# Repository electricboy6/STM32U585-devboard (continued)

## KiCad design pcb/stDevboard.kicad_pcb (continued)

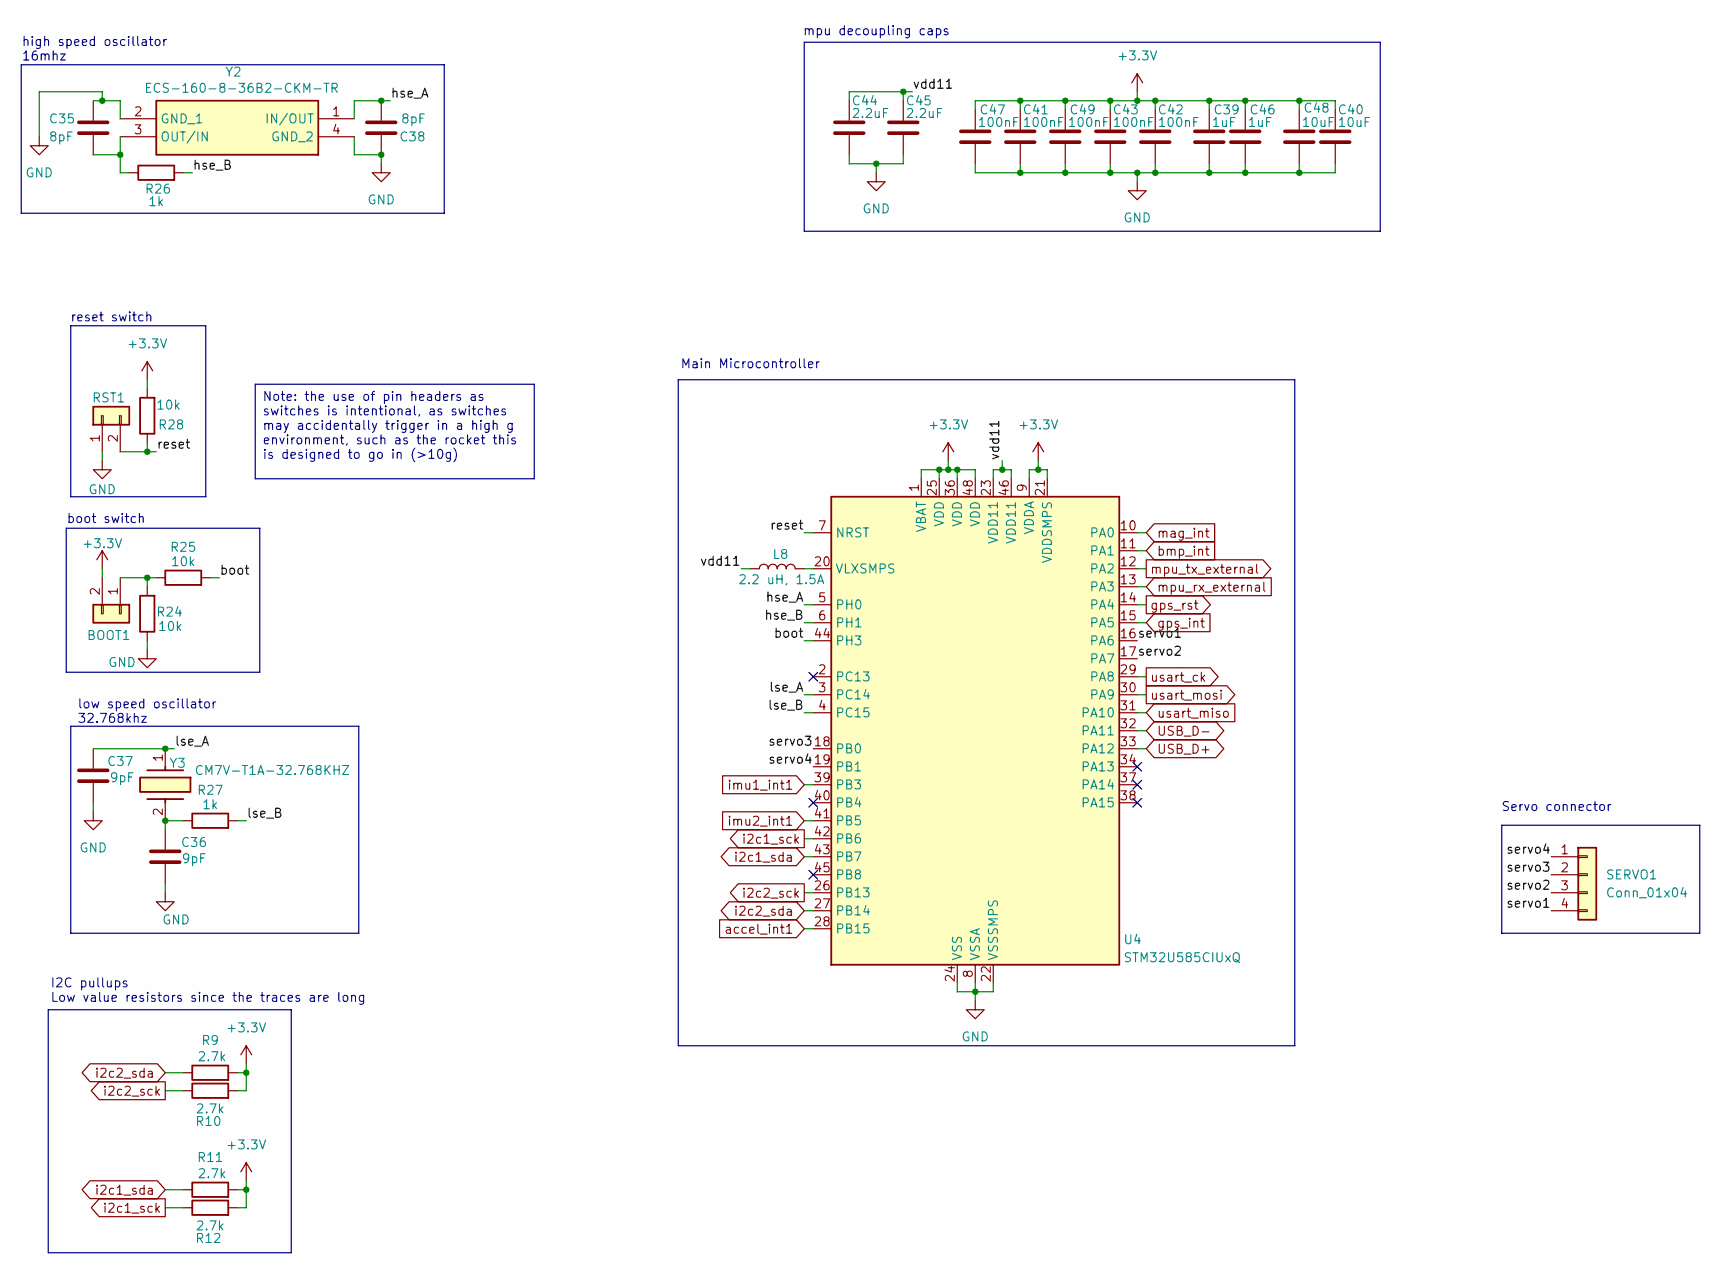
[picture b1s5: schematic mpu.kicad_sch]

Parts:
BOOT1: Conn_01x02; PinHeader_1x02_P2.54mm_Vertical
C35, C38: 8pF; C_0402_1005Metric
C36, C37: 9pF; C_0402_1005Metric
C39, C46: 1uF; C_0603_1608Metric
C40, C48: 10uF; C_0603_1608Metric
C41, C42, C43, C47, C49: 100nF; C_0402_1005Metric
C44, C45: 2.2uF; C_0603_1608Metric
L8: 2.2 uH, 1.5A; INDC2520X120N
R9, R10, R11, R12: 2.7k; R_0402_1005Metric
R24, R25, R28: 10k; R_0402_1005Metric
R26, R27: 1k; R_0402_1005Metric
RST1: Conn_01x02; PinHeader_1x02_P2.54mm_Vertical
SERVO1: Conn_01x04; TBC05041GG
U4: STM32U585CIUxQ; QFN-48-1EP_7x7mm_P0.5mm_EP5.6x5.6mm
Y2: ECS-160-8-36B2-CKM-TR; ECS160836B2CKMTR; Mouser Part Number 520-160-8-36B2-CKMTR
Y3: CM7V-T1A-32.768KHZ; CM7V32768TBQA020; Mouser Part Number 428-201565-MG01

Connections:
/main micro/boot: R25.2, U4.44 (PH3)
/main micro/hse_A: C38.1, U4.5 (PH0), Y2.1 (IN/OUT)
/main micro/hse_B: R26.2, U4.6 (PH1)
/main micro/lse_A: C37.1, U4.3 (PC14), Y3.1
/main micro/lse_B: R27.2, U4.4 (PC15)
/main micro/reset: R28.1, RST1.2, U4.7 (NRST)
/main micro/servo1: SERVO1.4, U4.16 (PA6)
/main micro/servo2: SERVO1.3, U4.17 (PA7)
/main micro/servo3: SERVO1.2, U4.18 (PB0)
/main micro/servo4: SERVO1.1, U4.19 (PB1)
/main micro/vdd11: C44.1, C45.1, L8.1, U4.23 (VDD11), U4.46 (VDD11)
GND: C35.2, C36.2, C37.2, C38.2, C39.2, C40.2, C41.2, C42.2, C43.2, C44.2, C45.2, C46.2, C47.2, C48.2, C49.2, R24.1, RST1.1, U4.8 (VSSA), U4.22 (VSSSMPS), U4.24 (VSS), U4.35 (VSS), U4.47 (VSS), U4.49 (VSS), Y2.2 (GND_1), Y2.4 (GND_2); also elsewhere on the board
unnamed: BOOT1.1, R24.2, R25.1
unnamed: C36.1, R27.1, Y3.2
unnamed: L8.2, U4.20 (VLXSMPS)
unnamed: C35.1, R26.1, Y2.3 (OUT/IN)
USB_D+: U4.33 (PA12); also elsewhere on the board
USB_D-: U4.32 (PA11); also elsewhere on the board
accel_int1: U4.28 (PB15); also elsewhere on the board
bmp_int: U4.11 (PA1); also elsewhere on the board
gps_int: U4.15 (PA5); also elsewhere on the board
gps_rst: U4.14 (PA4); also elsewhere on the board
i2c1_sck: R12.1, U4.42 (PB6); also elsewhere on the board
i2c1_sda: R11.1, U4.43 (PB7); also elsewhere on the board
i2c2_sck: R10.1, U4.26 (PB13); also elsewhere on the board
i2c2_sda: R9.1, U4.27 (PB14); also elsewhere on the board
imu1_int1: U4.39 (PB3); also elsewhere on the board
imu2_int1: U4.41 (PB5); also elsewhere on the board
mag_int: U4.10 (PA0); also elsewhere on the board
mpu_rx_external: U4.13 (PA3); also elsewhere on the board
mpu_tx_external: U4.12 (PA2); also elsewhere on the board
usart_ck: U4.29 (PA8); also elsewhere on the board
usart_miso: U4.31 (PA10); also elsewhere on the board
usart_mosi: U4.30 (PA9); also elsewhere on the board

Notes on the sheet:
I2C pullups Low value resistors since the traces are long
Main Microcontroller
mpu decoupling caps
Servo connector
high speed oscillator 16mhz
boot switch
reset switch
low speed oscillator 32.768khz
Note: the use of pin headers as switches is intentional, as switches may accidentally trigger in a high g environment, such as the rocket this is designed to go in (>10g)

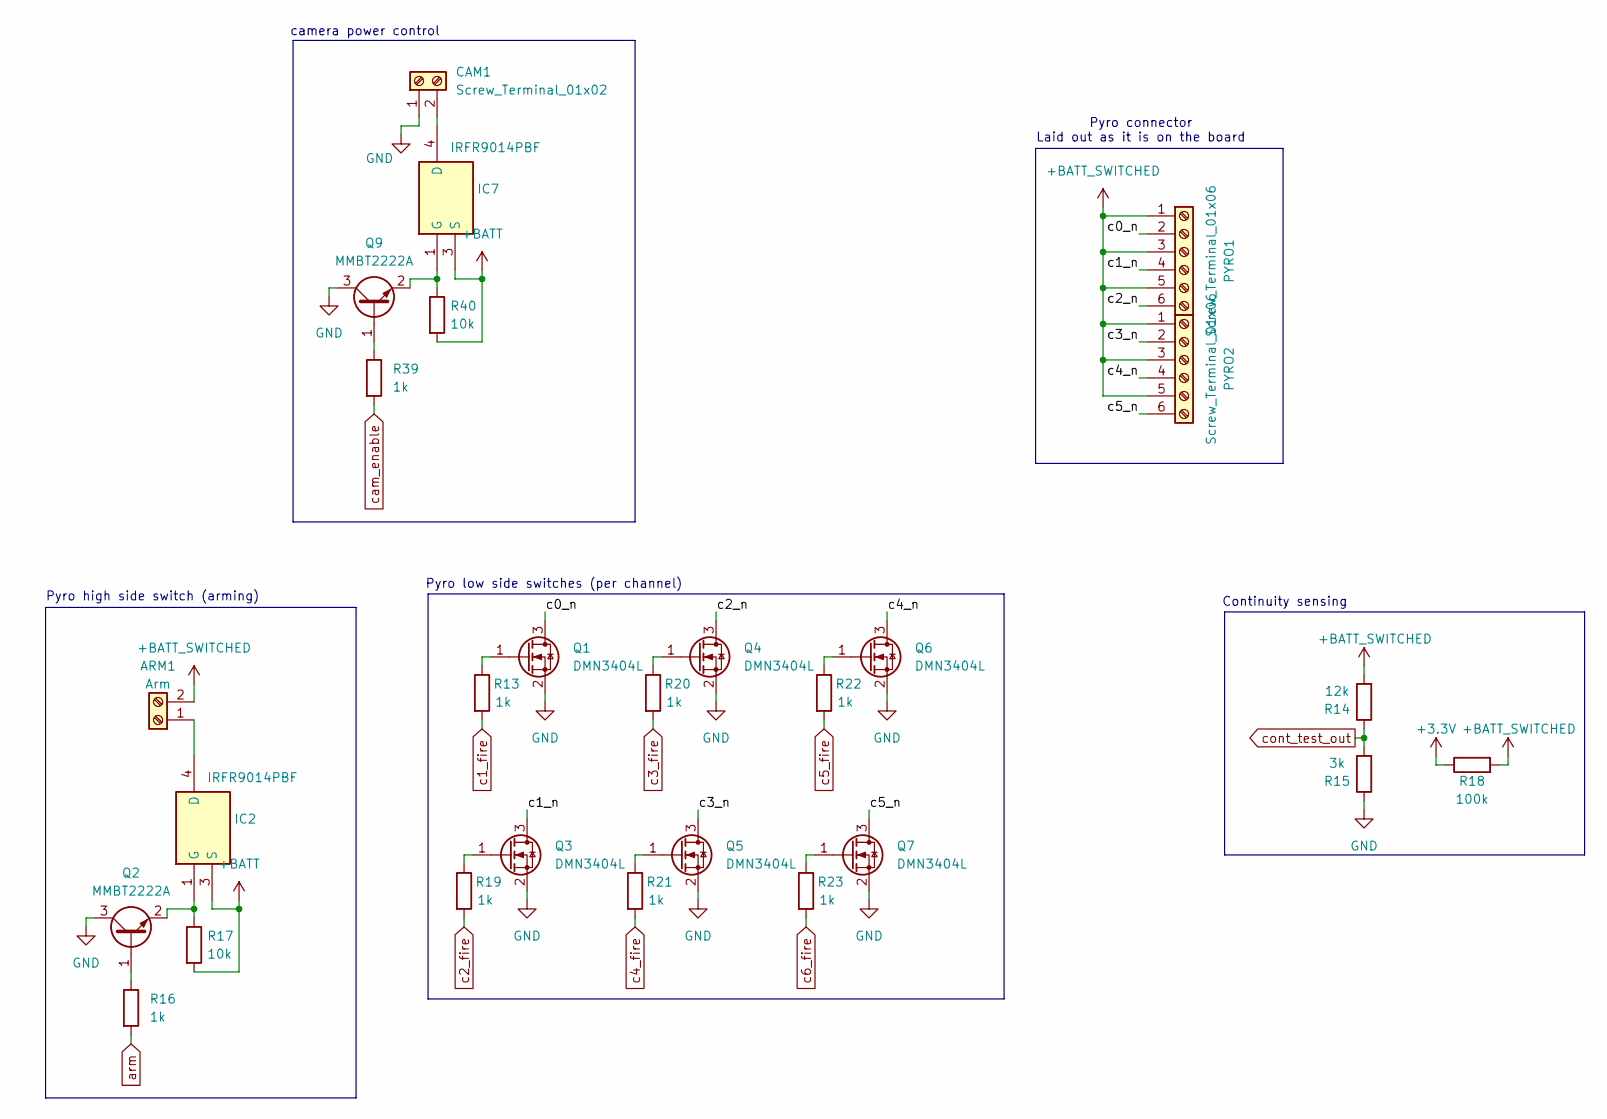
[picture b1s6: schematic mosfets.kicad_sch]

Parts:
ARM1: Arm; TBC05021GG
CAM1: Screw_Terminal_01x02; TBC05021GG
IC2, IC7: IRFR9014PBF; TO228P990X238-3N; Mouser Part Number 844-IRFR9014PBF
PYRO1, PYRO2: Screw_Terminal_01x06; TBC05061GG
Q1, Q3, Q4, Q5, Q6, Q7: DMN3404L; SOT-23
Q2, Q9: MMBT2222A; SOT-23
R13, R16, R19, R20, R21, R22, R23, R39: 1k; R_0402_1005Metric
R14: 12k; R_0402_1005Metric
R15: 3k; R_0402_1005Metric
R17, R40: 10k; R_0402_1005Metric
R18: 100k; R_0402_1005Metric

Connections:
+BATT: IC2.3 (S), IC7.3 (S), R17.2, R40.2; also elsewhere on the board
+BATT_SWITCHED: ARM1.2, PYRO1.1, PYRO1.3, PYRO1.5, PYRO2.1, PYRO2.3, PYRO2.5, R14.2, R18.2
/mosfets/c0_n: PYRO1.2, Q1.3 (D)
/mosfets/c1_n: PYRO1.4, Q3.3 (D)
/mosfets/c2_n: PYRO1.6, Q4.3 (D)
/mosfets/c3_n: PYRO2.2, Q5.3 (D)
/mosfets/c4_n: PYRO2.4, Q6.3 (D)
/mosfets/c5_n: PYRO2.6, Q7.3 (D)
GND: CAM1.1, Q1.2 (S), Q2.3 (C), Q3.2 (S), Q4.2 (S), Q5.2 (S), Q6.2 (S), Q7.2 (S), Q9.3 (C), R15.1; also elsewhere on the board
unnamed: ARM1.1, IC2.4 (D)
unnamed: CAM1.2, IC7.4 (D)
unnamed: IC2.1 (G), Q2.2 (E), R17.1
unnamed: IC7.1 (G), Q9.2 (E), R40.1
unnamed: Q1.1 (G), R13.1
unnamed: Q2.1 (B), R16.1
unnamed: Q3.1 (G), R19.1
unnamed: Q4.1 (G), R20.1
unnamed: Q5.1 (G), R21.1
unnamed: Q6.1 (G), R22.1
unnamed: Q7.1 (G), R23.1
unnamed: Q9.1 (B), R39.1
arm: R16.2; also elsewhere on the board
c1_fire: R13.2; also elsewhere on the board
c2_fire: R19.2; also elsewhere on the board
c3_fire: R20.2; also elsewhere on the board
c4_fire: R21.2; also elsewhere on the board
c5_fire: R22.2; also elsewhere on the board
c6_fire: R23.2; also elsewhere on the board
cam_enable: R39.2; also elsewhere on the board
cont_test_out: R14.1, R15.2; also elsewhere on the board

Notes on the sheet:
camera power control
Pyro low side switches (per channel)
Pyro high side switch (arming)
Continuity sensing
Pyro connector Laid out as it is on the board

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
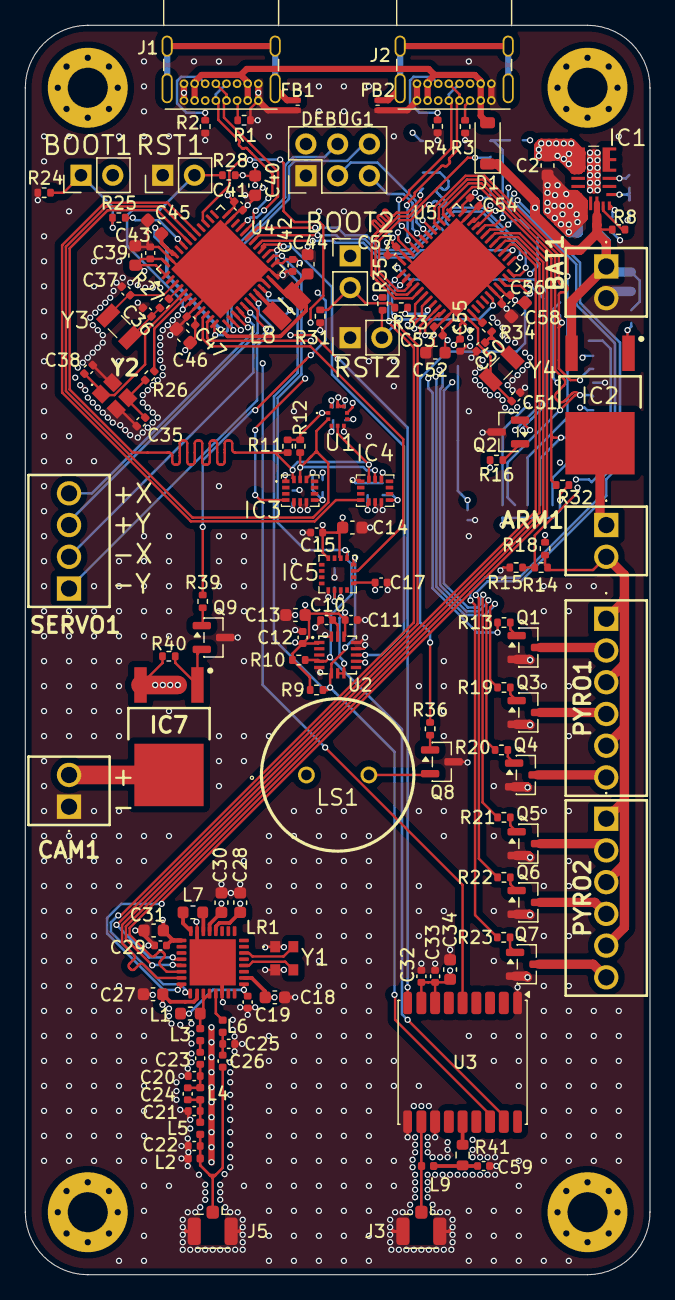
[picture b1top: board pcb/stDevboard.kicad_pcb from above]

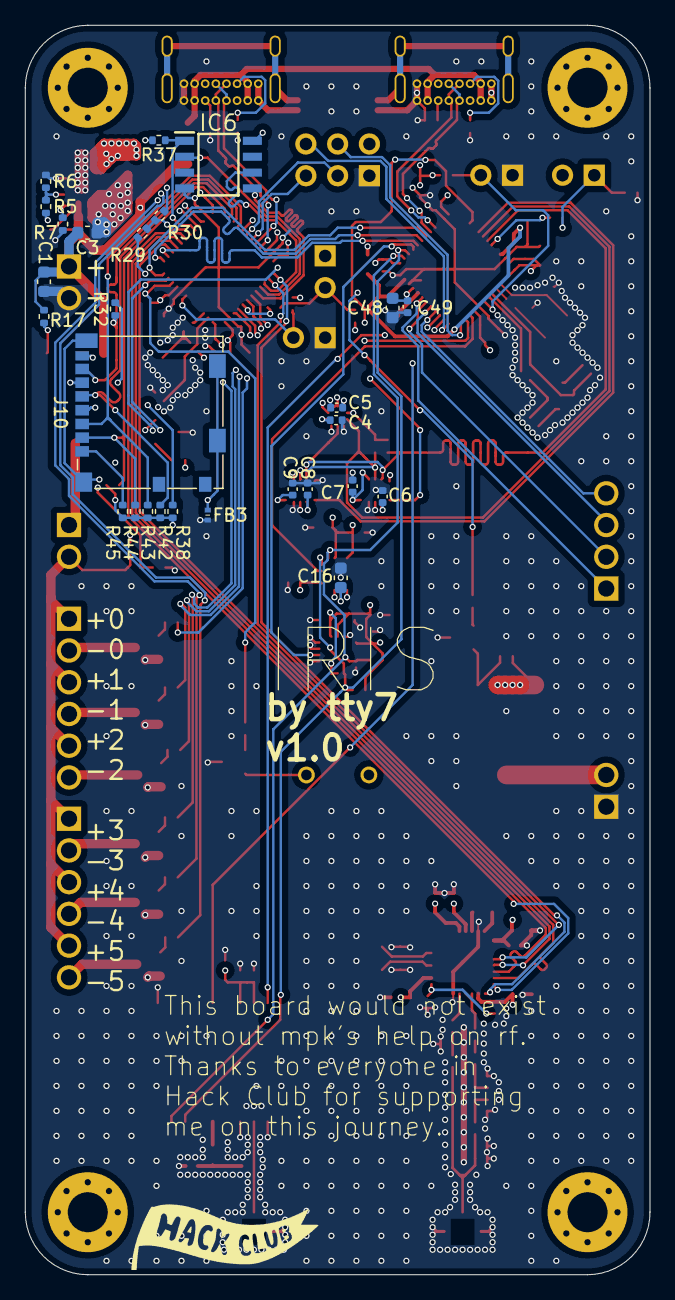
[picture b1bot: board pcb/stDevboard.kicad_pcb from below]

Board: 4 copper layers, 50.0 x 100.0 mm, 161 parts (27 on the bottom side), 122 nets.

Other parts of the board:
R32#2: 10k; R_0402_1005Metric

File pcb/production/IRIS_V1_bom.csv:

Designator,Footprint,Quantity,Value,LCSC Part #
ARM1,TBC05021GG,1,Arm,
BAT1,TBC05021GG,1,battery,
"BOOT1, BOOT2, RST1, RST2",PinHeader_1x02_P2.54mm_Vertical,4,Conn_01x02,
"C1, C2",0603,2,22uF,
"C10, C11, C12, C15, C17, C29, C32, C33, C4, C41, C42, C43, C47, C49, C5, C53, C54, C55, C56, C57, C6, C7, C8, C9",0402,24,100nF,
"C13, C16, C3, C34, C40, C48, C52",0603,7,10uF,
"C14, C27, C28, C39, C46, C58",0603,6,1uF,
"C18, C30, C44, C45",0603,4,2.2uF,
C19,0402,1,47pF,
C20,0402,1,7.5pF,
C21,0402,1,3.9pF,
"C22, C24",0402,2,1.8pF,
C23,0402,1,22pF,
C25,0402,1,2.2pF,
C26,0402,1,18pF,
C31,0603,1,4.7uF,
"C35, C38",0402,2,8pF,
"C36, C37, C50, C51",0402,4,9pF,
C59,0402,1,10nF,
CAM1,TBC05021GG,1,Screw_Terminal_01x02,
D1,D_SOD-123,1,D_Schottky,
DEBUG1,PinHeader_2x03_P2.54mm_Vertical,1,Conn_02x03_Top_Bottom,
"FB1, FB2, FB3",NFZ15SG152SN10B,3,BLM15AX102SN1D,
IC1,MPM3606GQVZ,1,MPM3610GQV-Z,
"IC2, IC7",TO228P990X238-3N,2,IRFR9014PBF,
"IC3, IC4",ICM42670P,2,ICM-45686,
IC5,MMC5983MA,1,MMC5983MA,
IC6,SOIC127P600X175-8N,1,AT25SF041B-SSHB-B,
"J1, J2",USB_C_Receptacle_GCT_USB4085,2,USB_C_Receptacle_USB2.0_16P,
J10,microSD_HC_Molex_104031-0811,1,Micro_SD_Card_Det2,
"J3, J5",U.FL_Hirose_U.FL-R-SMT-1_Vertical,2,Conn_Coaxial,
L1,0603,1,12nH,
L2,0402,1,22nH,
L3,0402,1,4.7nH,
L4,0402,1,3.9nH,
L5,0402,1,7.5nH,
L6,0402,1,24nH,
L7,0603,1,2.2uH,
L8,INDC2520X120N,1,"2.2 uH, 1.5A",
L9,0402,1,27nH,
LR1,LR2021,1,~,
LS1,PS1240P02BT,1,PS1240P02BT,
"PYRO1, PYRO2",TBC05061GG,2,Screw_Terminal_01x06,
"Q1, Q3, Q4, Q5, Q6, Q7",SOT-23,6,DMN3404L,
"Q2, Q8, Q9",SOT-23,3,MMBT2222A,
"R1, R2, R3, R4",0402,4,5.1K,
"R10, R11, R12, R9",0402,4,2.7k,
"R13, R16, R19, R20, R21, R22, R23, R26, R27, R34, R36, R39",0402,12,1k,
"R14, R29",0402,2,12k,
"R15, R30",0402,2,3k,
"R17, R24, R25, R28, R31, R32, R33, R35, R37, R38, R40, R42, R43, R44, R45",0402,15,10k,
"R18, R32_2, R8",0402,3,100k,
R41,0603,1,10,
R5,0402,1,75k,
R6,0402,1,24k,
R7,0402,1,39k,
SERVO1,TBC05041GG,1,Conn_01x04,
U1,BMP581,1,BMP581,
U3,ublox_MAX,1,MAX-M10S,
U4,QFN-48-1EP_7x7mm_P0.5mm_EP5.6x5.6mm,1,STM32U585CIUxQ,
U5,QFN-48-1EP_7x7mm_P0.5mm_EP5.6x5.6mm,1,STM32U073CCUx,
Y1,ECSTXO25CSMV320AMTR,1,ECS-TXO-25CSMV-320-AM-TR,
Y2,ECS160836B2CKMTR,1,ECS-160-8-36B2-CKM-TR,
"Y3, Y4",CM7V32768TBQA020,2,CM7V-T1A-32.768KHZ,

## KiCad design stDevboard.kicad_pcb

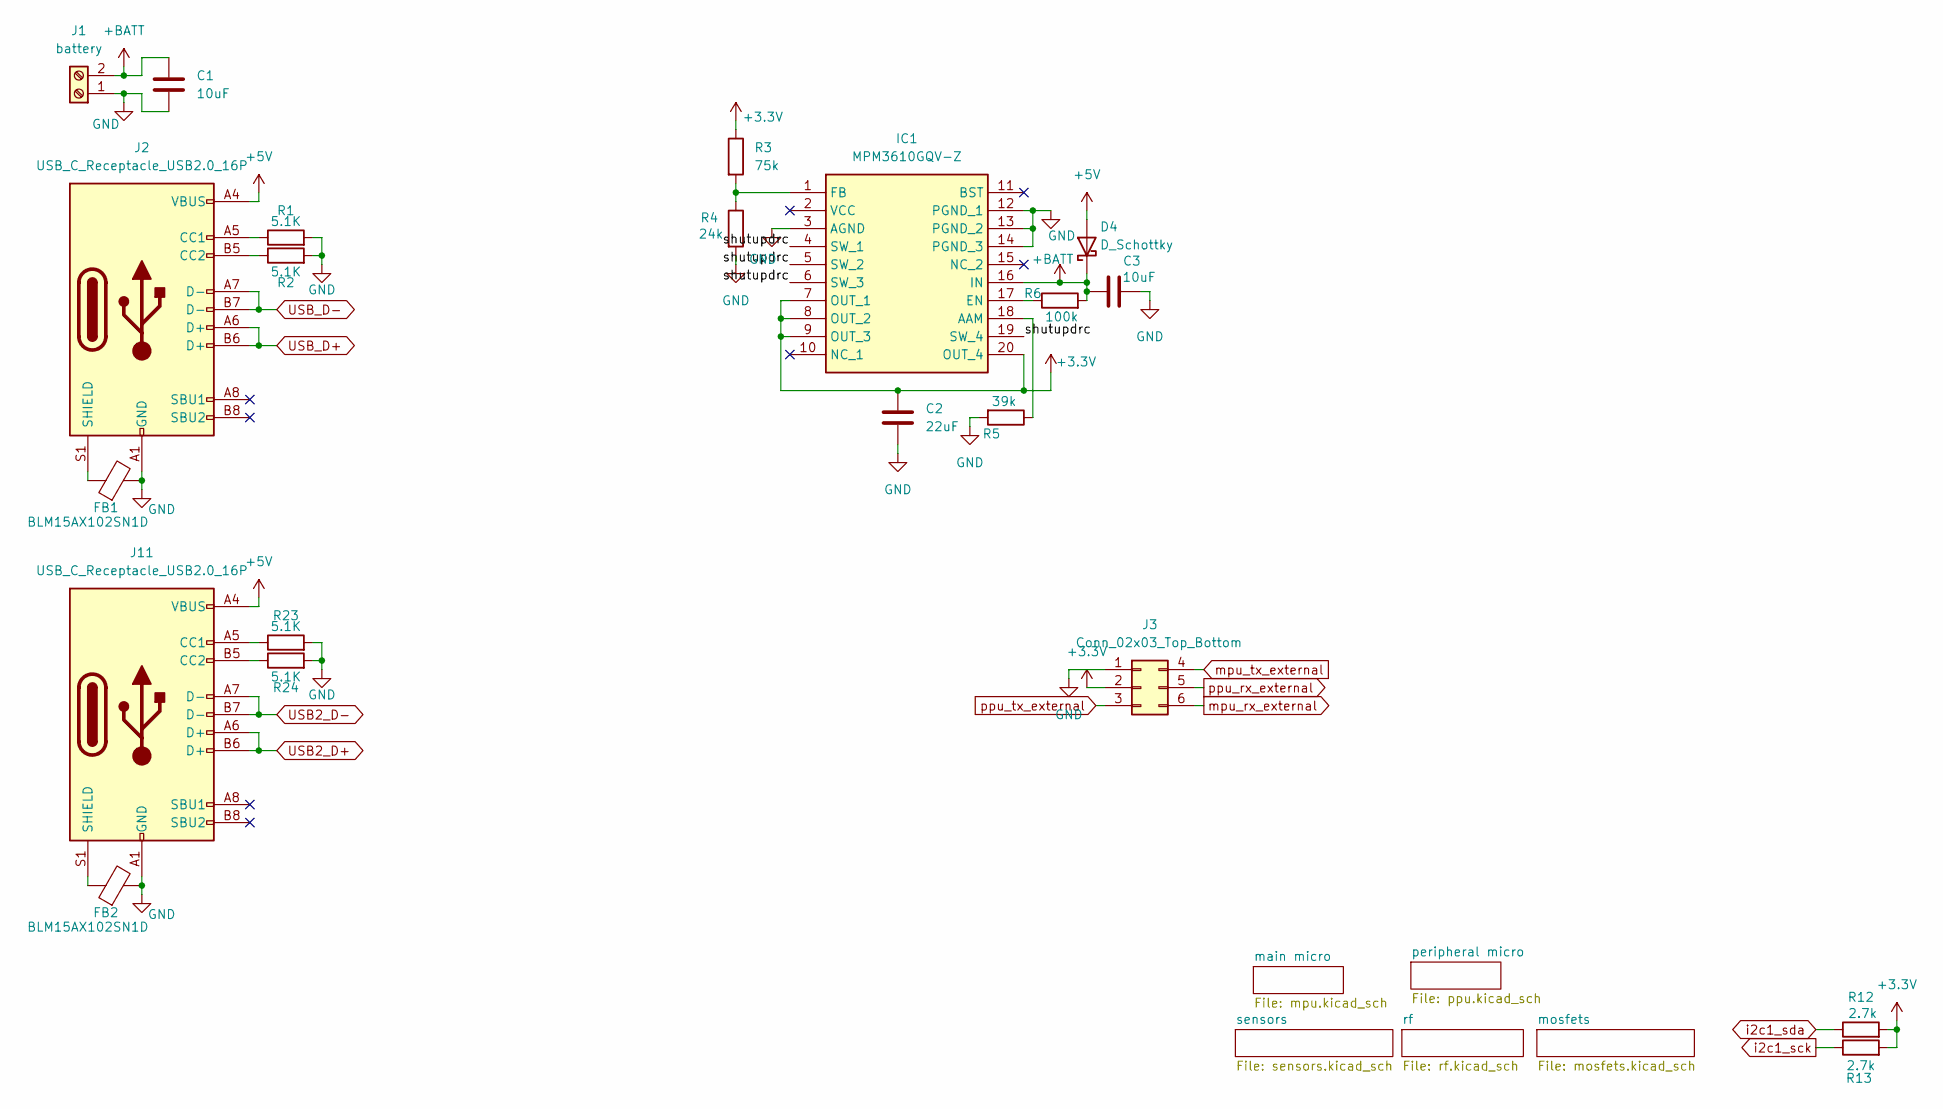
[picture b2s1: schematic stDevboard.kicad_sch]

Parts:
C1: 10uF; C_0805_2012Metric
C2: 22uF; C_0603_1608Metric
C3: 10uF; C_0603_1608Metric
D4: D_Schottky; D_0805_2012Metric
FB1, FB2: BLM15AX102SN1D; NFZ15SG152SN10B
IC1: MPM3610GQV-Z; MPM3606GQVZ; Mouser Part Number 946-MPM3610GQV-Z
J1: battery; TerminalBlock_Xinya_XY308-2.54-2P_1x02_P2.54mm_Horizontal
J2, J11: USB_C_Receptacle_USB2.0_16P; USB_C_Receptacle_GCT_USB4085
J3: Conn_02x03_Top_Bottom; PinHeader_2x03_P2.54mm_Vertical
R1, R2, R23, R24: 5.1K; R_0402_1005Metric
R3: 75k; R_0201_0603Metric
R4: 24k; R_0201_0603Metric
R5: 39k; R_0201_0603Metric
R6: 100k; R_0402_1005Metric
R12, R13: 2.7k; R_0402_1005Metric

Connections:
+3.3V: C2.2, IC1.7 (OUT_1), IC1.8 (OUT_2), IC1.9 (OUT_3), IC1.20 (OUT_4), J3.2, R3.1, R12.2, R13.2; also elsewhere on the board
+5V: D4.2 (A), J2.A4 (VBUS), J2.A9 (VBUS), J2.B4 (VBUS), J2.B9 (VBUS), J11.A4 (VBUS), J11.A9 (VBUS), J11.B4 (VBUS), J11.B9 (VBUS)
+BATT: C1.1, C3.1, D4.1 (K), IC1.16 (IN), J1.2, R6.2; also elsewhere on the board
/shutupdrc: IC1.4 (SW_1), IC1.5 (SW_2), IC1.6 (SW_3), IC1.19 (SW_4)
GND: C1.2, C2.1, C3.2, FB1.2, FB2.2, IC1.3 (AGND), IC1.12 (PGND_1), IC1.13 (PGND_2), IC1.14 (PGND_3), J1.1, J2.A1 (GND), J2.A12 (GND), J2.B1 (GND), J2.B12 (GND), J3.1, J11.A1 (GND), J11.A12 (GND), J11.B1 (GND), J11.B12 (GND), R1.2, R2.2, R4.2, R5.2, R23.2, R24.2; also elsewhere on the board
unnamed: IC1.18 (AAM), R5.1
unnamed: IC1.17 (EN), R6.1
unnamed: IC1.1 (FB), R3.2, R4.1
unnamed: J2.A5 (CC1), R1.1
unnamed: J2.B5 (CC2), R2.1
unnamed: FB1.1, J2.S1 (SHIELD)
unnamed: J11.A5 (CC1), R23.1
unnamed: J11.B5 (CC2), R24.1
unnamed: FB2.1, J11.S1 (SHIELD)
USB2_D+: J11.A6 (D+), J11.B6 (D+); also elsewhere on the board
USB2_D-: J11.A7 (D-), J11.B7 (D-); also elsewhere on the board
USB_D+: J2.A6 (D+), J2.B6 (D+); also elsewhere on the board
USB_D-: J2.A7 (D-), J2.B7 (D-); also elsewhere on the board
i2c1_sck: R13.1; also elsewhere on the board
i2c1_sda: R12.1; also elsewhere on the board
mpu_rx_external: J3.6; also elsewhere on the board
mpu_tx_external: J3.4; also elsewhere on the board
ppu_rx_external: J3.5; also elsewhere on the board
ppu_tx_external: J3.3; also elsewhere on the board

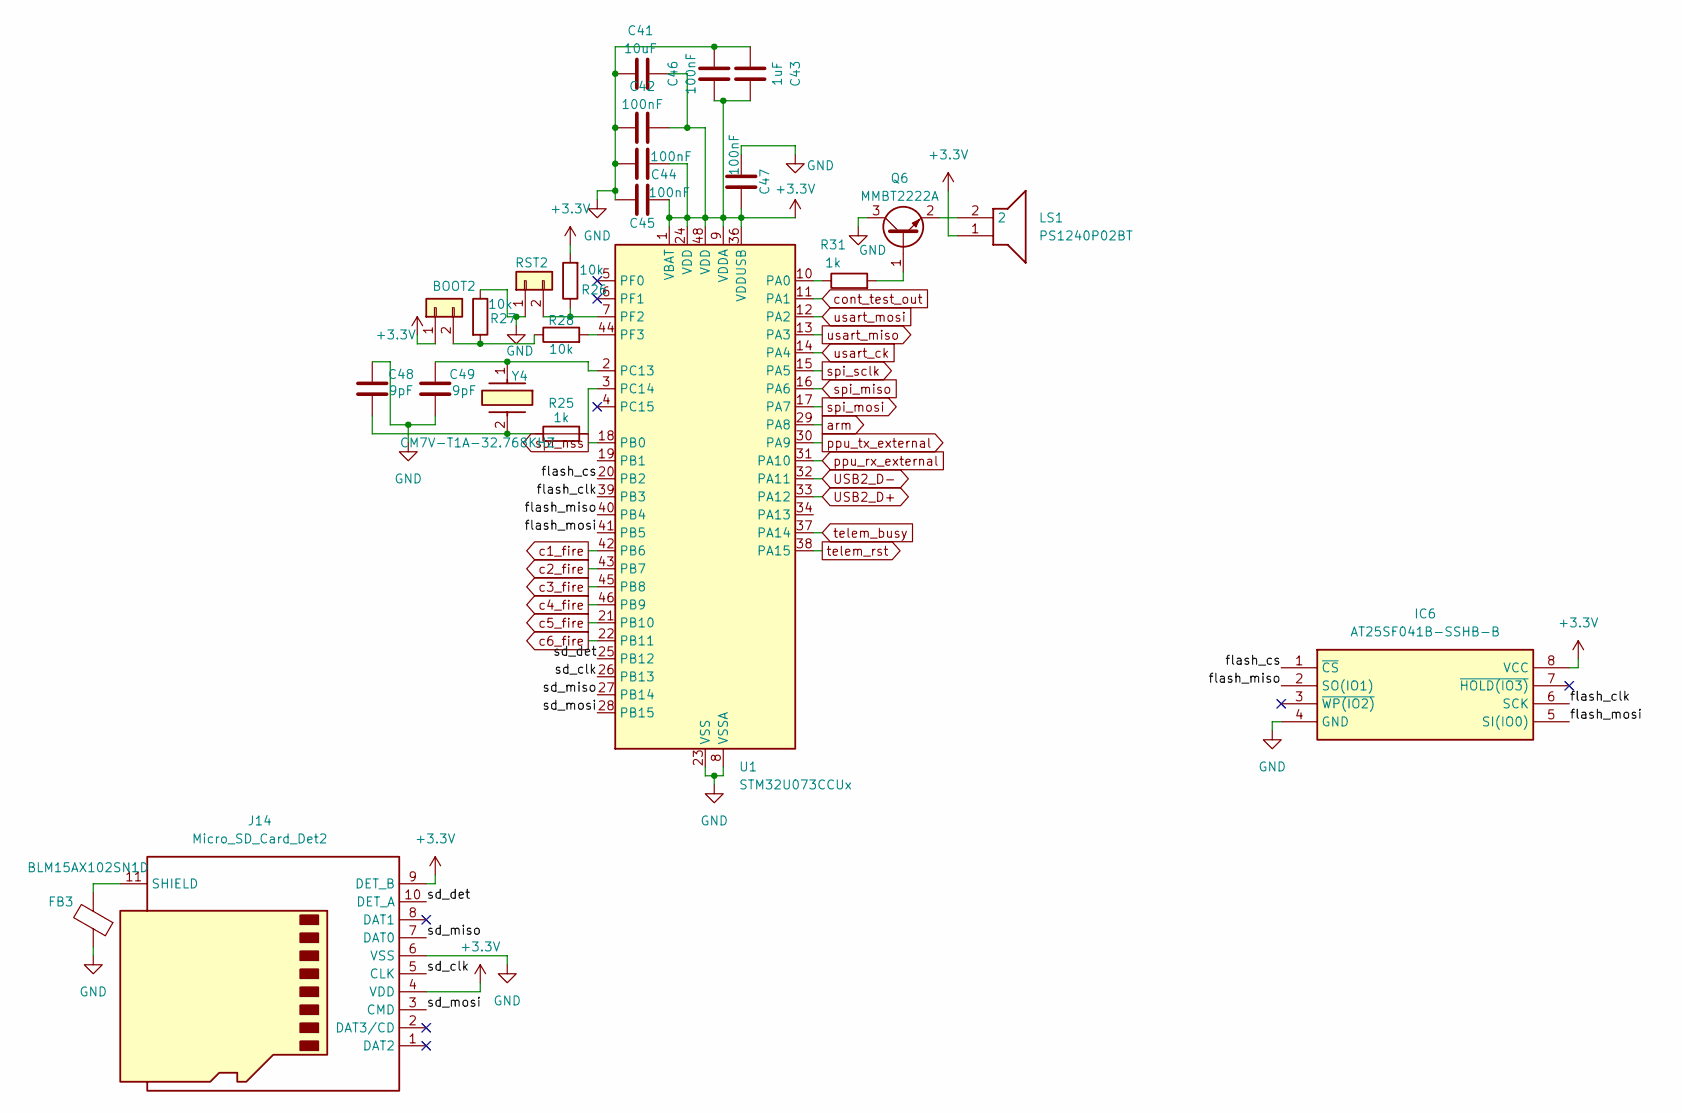
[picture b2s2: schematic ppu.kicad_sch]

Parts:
BOOT2: Conn_01x02; PinHeader_1x02_P2.54mm_Vertical
C41: 10uF; C_0603_1608Metric
C42, C44, C45, C46, C47: 100nF; C_0402_1005Metric
C43: 1uF; C_0603_1608Metric
C48, C49: 9pF; C_0402_1005Metric
FB3: BLM15AX102SN1D; NFZ15SG152SN10B
IC6: AT25SF041B-SSHB-B; SOIC127P600X175-8N; Mouser Part Number 988-AT25SF041-SSH-B
J14: Micro_SD_Card_Det2; microSD_HC_Molex_104031-0811
LS1: PS1240P02BT; Mouser Part Number 810-PS1240P02BT
Q6: MMBT2222A; SOT-23
R25, R31: 1k; R_0402_1005Metric
R26, R27, R28: 10k; R_0402_1005Metric
RST2: Conn_01x02; PinHeader_1x02_P2.54mm_Vertical
U1: STM32U073CCUx; QFN-48-1EP_7x7mm_P0.5mm_EP5.6x5.6mm
Y4: CM7V-T1A-32.768KHZ; CM7V32768TBQA020; Mouser Part Number 428-201565-MG01

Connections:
+3.3V: BOOT2.1, C41.2, C42.2, C43.2, C44.1, C45.1, C46.1, C47.2, IC6.8 (VCC), J14.4 (VDD), J14.9 (DET_B), LS1.1, R26.2, U1.1 (VBAT), U1.9 (VDDA), U1.24 (VDD), U1.36 (VDDUSB), U1.48 (VDD); also elsewhere on the board
/peripheral micro/flash_clk: IC6.6 (SCK), U1.39 (PB3)
/peripheral micro/flash_cs: IC6.1 (~CS), U1.20 (PB2)
/peripheral micro/flash_miso: IC6.2 (SO(IO1)), U1.40 (PB4)
/peripheral micro/flash_mosi: IC6.5 (SI(IO0)), U1.41 (PB5)
/peripheral micro/sd_clk: J14.5 (CLK), U1.26 (PB13)
/peripheral micro/sd_det: J14.10 (DET_A), U1.25 (PB12)
/peripheral micro/sd_miso: J14.7 (DAT0), U1.27 (PB14)
/peripheral micro/sd_mosi: J14.3 (CMD), U1.28 (PB15)
GND: C41.1, C42.1, C43.1, C44.2, C45.2, C46.2, C47.1, C48.1, C49.2, FB3.1, IC6.4 (GND), J14.6 (VSS), Q6.3 (C), R27.1, RST2.1, U1.8 (VSSA), U1.23 (VSS), U1.35 (VSS), U1.47 (VSS), U1.49 (VSS); also elsewhere on the board
unnamed: BOOT2.2, R27.2, R28.1
unnamed: C48.2, R25.1, Y4.2
unnamed: FB3.2, J14.11 (SHIELD)
unnamed: Q6.1 (B), R31.2
unnamed: LS1.2, Q6.2 (E)
unnamed: R26.1, RST2.2, U1.7 (PF2)
unnamed: R31.1, U1.10 (PA0)
unnamed: C49.1, U1.2 (PC13), Y4.1
unnamed: R25.2, U1.3 (PC14)
unnamed: R28.2, U1.44 (PF3)
USB2_D+: U1.33 (PA12); also elsewhere on the board
USB2_D-: U1.32 (PA11); also elsewhere on the board
arm: U1.29 (PA8); also elsewhere on the board
c1_fire: U1.42 (PB6); also elsewhere on the board
c2_fire: U1.43 (PB7); also elsewhere on the board
c3_fire: U1.45 (PB8); also elsewhere on the board
c4_fire: U1.46 (PB9); also elsewhere on the board
c5_fire: U1.21 (PB10); also elsewhere on the board
c6_fire: U1.22 (PB11); also elsewhere on the board
cont_test_out: U1.11 (PA1); also elsewhere on the board
ppu_rx_external: U1.31 (PA10); also elsewhere on the board
ppu_tx_external: U1.30 (PA9); also elsewhere on the board
spi_miso: U1.16 (PA6); also elsewhere on the board
spi_mosi: U1.17 (PA7); also elsewhere on the board
spi_nss: U1.18 (PB0); also elsewhere on the board
spi_sclk: U1.15 (PA5); also elsewhere on the board
telem_busy: U1.37 (PA14); also elsewhere on the board
telem_rst: U1.38 (PA15); also elsewhere on the board
usart_ck: U1.14 (PA4); also elsewhere on the board
usart_miso: U1.13 (PA3); also elsewhere on the board
usart_mosi: U1.12 (PA2); also elsewhere on the board

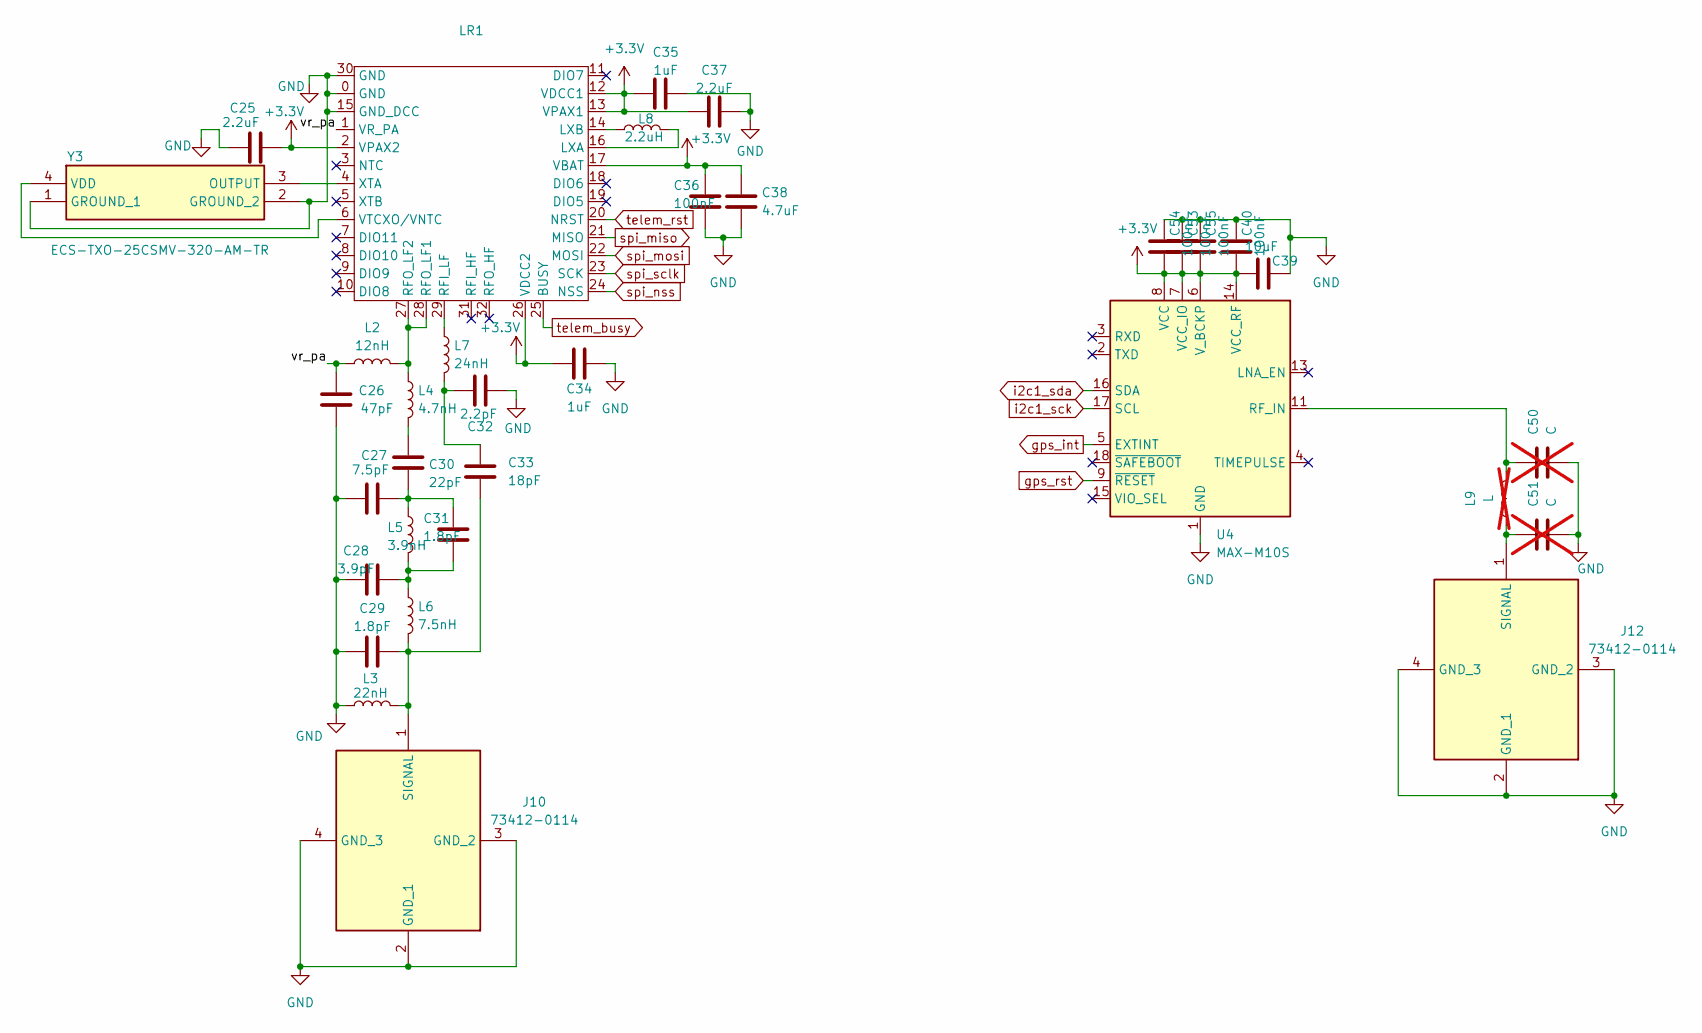
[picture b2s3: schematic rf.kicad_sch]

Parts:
C25, C37: 2.2uF; C_0603_1608Metric
C26: 47pF; C_0402_1005Metric
C27: 7.5pF; C_0402_1005Metric
C28: 3.9pF; C_0402_1005Metric
C29, C31: 1.8pF; C_0402_1005Metric
C30: 22pF; C_0402_1005Metric
C32: 2.2pF; C_0402_1005Metric
C33: 18pF; C_0402_1005Metric
C34, C35: 1uF; C_0603_1608Metric
C36, C40, C53, C54, C55: 100nF; C_0402_1005Metric
C38: 4.7uF; C_0603_1608Metric
C39: 10uF; C_0603_1608Metric
C50, C51: C; C_0402_1005Metric; not fitted
J10, J12: 73412-0114; 73412-0110; Mouser Part Number 538-73412-0114
L2: 12nH; L_0603_1608Metric
L3: 22nH; L_0402_1005Metric
L4: 4.7nH; L_0402_1005Metric
L5: 3.9nH; L_0402_1005Metric
L6: 7.5nH; L_0402_1005Metric
L7: 24nH; L_0402_1005Metric
L8: 2.2uH; L_0805_2012Metric
L9: L; L_0402_1005Metric; not fitted
LR1: LR2021
U4: MAX-M10S; ublox_MAX
Y3: ECS-TXO-25CSMV-320-AM-TR; ECSTXO25CSMV320AMTR; Mouser Part Number 520-TXO25CSMV320AMTR

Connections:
+3.3V: C25.2, C34.1, C35.1, C36.1, C37.1, C38.1, C39.1, C40.1, C53.1, C54.1, C55.1, LR1.2 (VPAX2), LR1.12 (VDCC1), LR1.13 (VPAX1), LR1.17 (VBAT), LR1.26 (VDCC2), U4.6 (V_BCKP), U4.7 (VCC_IO), U4.8 (VCC), U4.14 (VCC_RF); also elsewhere on the board
/rf/vr_pa: C26.1, L2.1, LR1.1 (VR_PA)
GND: C25.1, C26.2, C27.1, C28.1, C29.1, C32.2, C34.2, C35.2, C36.2, C37.2, C38.2, C39.2, C40.2, C50.2, C51.2, C53.2, C54.2, C55.2, J10.2 (GND_1), J10.3 (GND_2), J10.4 (GND_3), J12.2 (GND_1), J12.3 (GND_2), J12.4 (GND_3), L3.1, LR1.0 (GND), LR1.15 (GND_DCC), LR1.30 (GND), U4.1 (GND), U4.10 (GND), U4.12 (GND), Y3.1 (GROUND_1), Y3.2 (GROUND_2); also elsewhere on the board
unnamed: C27.2, C30.2, C31.1, L5.1
unnamed: C28.2, C31.2, L5.2, L6.1
unnamed: C30.1, L4.2
unnamed: C32.1, C33.1, L7.2
unnamed: C29.2, C33.2, J10.1 (SIGNAL), L3.2, L6.2
unnamed: C51.1, J12.1 (SIGNAL), L9.1
unnamed: L8.2, LR1.16 (LXA)
unnamed: L8.1, LR1.14 (LXB)
unnamed: L7.1, LR1.29 (RFI_LF)
unnamed: L2.2, L4.1, LR1.27 (RFO_LF2), LR1.28 (RFO_LF1)
unnamed: LR1.6 (VTCXO/VNTC), Y3.4 (VDD)
unnamed: LR1.4 (XTA), Y3.3 (OUTPUT)
unnamed: C50.1, L9.2, U4.11 (RF_IN)
gps_int: U4.5 (EXTINT); also elsewhere on the board
gps_rst: U4.9 (~RESET); also elsewhere on the board
spi_miso: LR1.21 (MISO); also elsewhere on the board
spi_mosi: LR1.22 (MOSI); also elsewhere on the board
spi_nss: LR1.24 (NSS); also elsewhere on the board
spi_sclk: LR1.23 (SCK); also elsewhere on the board
telem_busy: LR1.25 (BUSY); also elsewhere on the board
telem_rst: LR1.20 (NRST); also elsewhere on the board
